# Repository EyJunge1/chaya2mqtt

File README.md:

Languages: **🇬🇧** | [🇩🇪](./.github/i18n/README.de.md)

Send a little heart to someone special—no matter how far away they are.

Chaya2MQTT pairs two people over [Waveshare ESP32-S3 e-paper displays](https://docs.waveshare.com/ESP32-S3-ePaper-1.54G)—each can have more than one board (home, office, …).

Press the button on yours and a red heart appears on theirs.

Every display keeps track of the hearts you have sent and received, while MQTT quietly carries them between you.

### Product

| Online                                                    | Product title                                             | SoftAP setup                                       | Offline                                                       | Power-off                                          |
| --------------------------------------------------------- | --------------------------------------------------------- | -------------------------------------------------- | ------------------------------------------------------------- | -------------------------------------------------- |
|  |  |  |  |  |

> [!NOTE]
> Open the [web flasher](https://eyjunge1.github.io/chaya2mqtt/) in Chrome or Edge, connect USB-C, and install.

### Case

Printable snap-fit case (battery + USB-only): [MakerWorld](https://makerworld.com/de/models/3505578-waveshare-esp32-s3-epaper-1-54-case-chaya2mqtt#profileId-4005122).

Remove the rear SPI header and the speaker before assembly.

## License

[GNU GPL v3.0 only](LICENSE)

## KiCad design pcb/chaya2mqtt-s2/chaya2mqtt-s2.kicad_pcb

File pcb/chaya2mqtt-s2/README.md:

# chaya2mqtt-s2 Rev A2

Compact four-layer 46.0 × 45.0 mm board for ESP32-S2-MINI-2-N4R2 and
GDEM0154F61H. The e-paper display is mounted at the front of the enclosure,
USB-C sits at the lower edge on the rear, and the illuminated button is
connected through J3.

## Target hardware

- ESP32-S2-MINI-2-N4R2: Wi-Fi, native USB, no Bluetooth, 4 MB flash, 2 MB PSRAM
- GDEM0154F61H: 1.54 inch, 200×200, black/white/red/yellow, SSD2681
- USB-C at the rear; display at the front; wired red LED ring button
- Four layers: F.Cu / In1.Cu GND / In2.Cu 3V3 / B.Cu

## Electrical blocks

- USB-C with 5.1 kΩ CC resistors, ESD protection, PTC, and 22 Ω series resistors
- TLV75733PDBVR (1 A) with input/output decoupling
- EN/BOOT, reset/boot buttons, and five test points
- 24-pin 0.5 mm FPC for the raw panel
- SSD2681 boost circuit according to GDEM0154F61H Rev 1.0 dated 2026-05-15

## Status

- The schematic is electrically complete; KiCad 10 ERC reports 0 violations.
- Unused MCU/panel pins are explicitly marked as `No Connect`.
- The 46 × 45 mm layout is fully routed; KiCad 10 DRC reports
  0 violations and 0 unconnected items.
- In1 contains a GND plane, and In2 contains a 3V3 plane. Both start below
  the ESP32 antenna keepout.
- KiCad sources, BOM, CPL, and manufacturing exports are located in `production/`.
- Two M2 holes at the bottom; the top remains free of holes due to the official
  antenna keepout.
- The board is a prototype. Electrical bring-up, e-paper high-voltage
  measurements, USB signal integrity testing, mechanical FPC/enclosure checks,
  and a 2.4 GHz RF test are required before a production order.

`../tools/generate_chaya2mqtt_s2_schematic.py` generates the schematic
reproducibly. `../tools/apply_schematic_netlist.py` maps the XML netlist
unambiguously onto the PCB, including duplicated footprint pads.
Manufacturing data, PDF, BOM, ERC, and DRC are exported with `kicad-cli`.

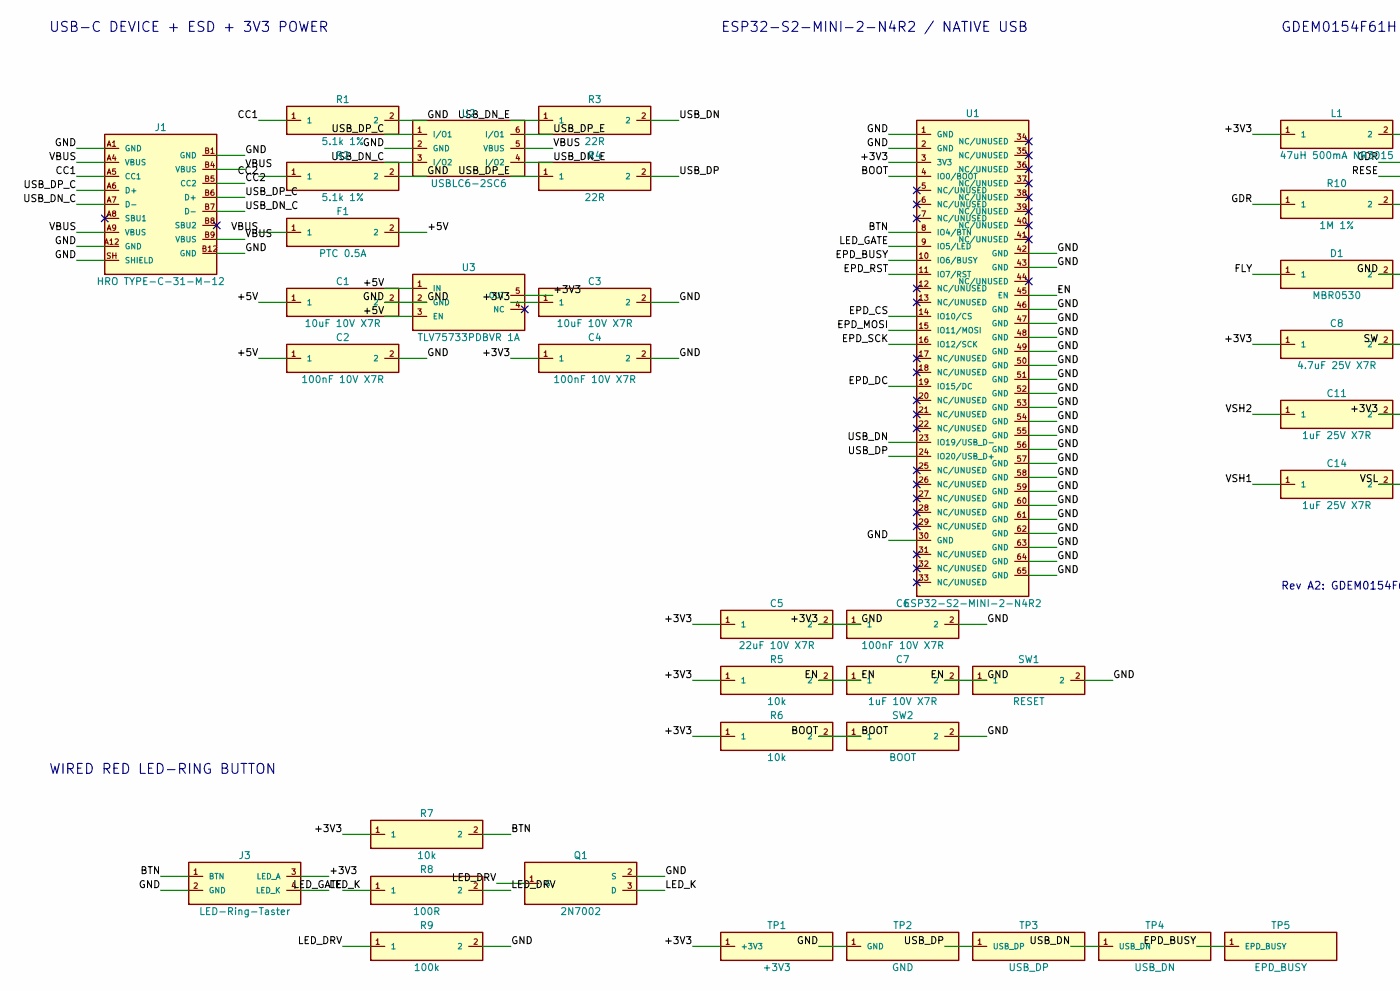
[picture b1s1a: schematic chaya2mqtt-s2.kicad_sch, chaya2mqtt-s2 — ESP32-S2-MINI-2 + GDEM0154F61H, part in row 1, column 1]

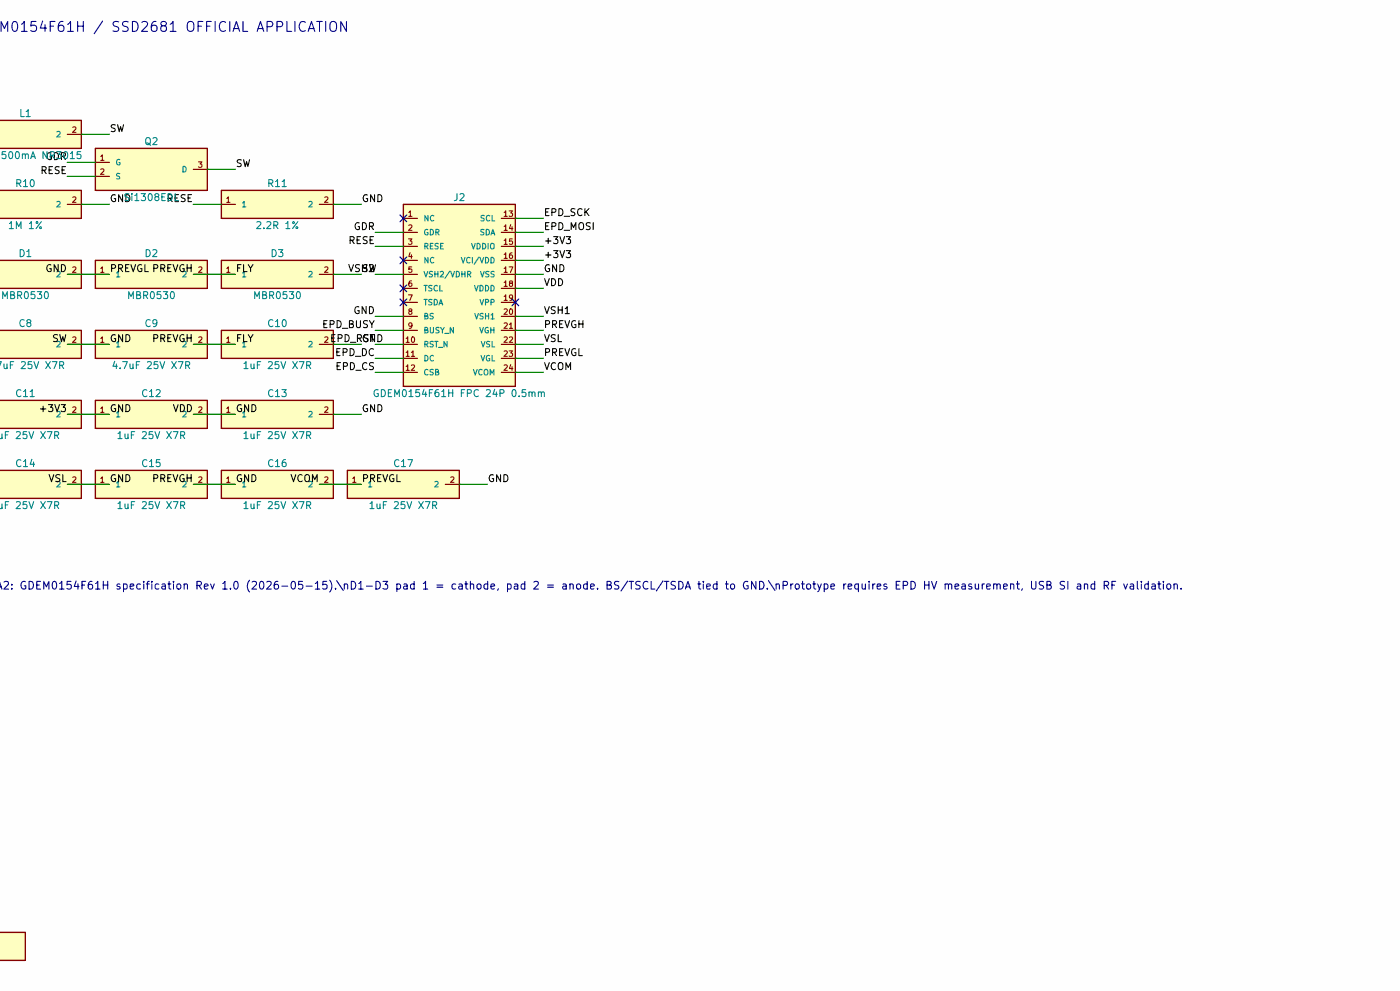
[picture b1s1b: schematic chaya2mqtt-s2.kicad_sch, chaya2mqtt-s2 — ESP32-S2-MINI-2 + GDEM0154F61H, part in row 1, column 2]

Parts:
C1, C3: 10uF 10V X7R; C_0805_2012Metric
C2, C4, C6: 100nF 10V X7R; C_0402_1005Metric
C5: 22uF 10V X7R; C_0805_2012Metric
C7: 1uF 10V X7R; C_0603_1608Metric
C8, C9: 4.7uF 25V X7R; C_0805_2012Metric
C10, C11, C12, C13, C14, C15, C16, C17: 1uF 25V X7R; C_0603_1608Metric
D1, D2, D3: MBR0530; D_SOD-123
F1: PTC 0.5A; Fuse_1206_3216Metric
J1: HRO TYPE-C-31-M-12; USB_C_Receptacle_HRO_TYPE-C-31-M-12; MPN TYPE-C-31-M-12
J2: GDEM0154F61H FPC 24P 0.5mm; Hirose_FH12-24S-0.5SH_1x24-1MP_P0.50mm_Horizontal; MPN GDEM0154F61H
J3: LED-Ring-Taster; JST_SH_SM04B-SRSS-TB_1x04-1MP_P1.00mm_Horizontal
L1: 47uH 500mA NR3015; L_Taiyo-Yuden_NR-30xx
Q1: 2N7002; SOT-23
Q2: Si1308EDL; SOT-323_SC-70; MPN SI1308EDL-T1-GE3
R1, R2: 5.1k 1%; R_0402_1005Metric
R3, R4: 22R; R_0402_1005Metric
R5, R6, R7: 10k; R_0402_1005Metric
R8: 100R; R_0402_1005Metric
R9: 100k; R_0402_1005Metric
R10: 1M 1%; R_0402_1005Metric
R11: 2.2R 1%; R_0603_1608Metric
SW1: RESET; SW_Push_1P1T_NO_CK_KMR2
SW2: BOOT; SW_Push_1P1T_NO_CK_KMR2
TP1: +3V3; TestPoint_Pad_D1.0mm
TP2: GND; TestPoint_Pad_D1.0mm
TP3: USB_DP; TestPoint_Pad_D1.0mm
TP4: USB_DN; TestPoint_Pad_D1.0mm
TP5: EPD_BUSY; TestPoint_Pad_D1.0mm
U1: ESP32-S2-MINI-2-N4R2; ESP32-S2-MINI-1; MPN ESP32-S2-MINI-2-N4R2
U2: USBLC6-2SC6; SOT-23-6; MPN USBLC6-2SC6
U3: TLV75733PDBVR 1A; SOT-23-5; MPN TLV75733PDBVR

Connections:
/+3V3: C3.1, C4.1, C5.1, C6.1, C8.1, C12.1, J2.15 (VDDIO), J2.16 (VCI/VDD), J3.3 (LED_A), L1.1, R5.1, R6.1, R7.1, TP1.1 (+3V3_1), U1.3 (3V3), U3.5 (OUT)
/+5V: C1.1, C2.1, F1.2, U3.1 (IN), U3.3 (EN)
/BOOT: R6.2, SW2.1, U1.4 (IO0/BOOT)
/BTN: J3.1 (BTN), R7.2, U1.8 (IO4/BTN)
/CC1: J1.A5 (CC1), R1.1
/CC2: J1.B5 (CC2), R2.1
/EN: C7.1, R5.2, SW1.1, U1.45 (EN)
/EPD_BUSY: J2.9 (BUSY_N), TP5.1 (EPD_BUSY_1), U1.10 (IO6/BUSY)
/EPD_CS: J2.12 (CSB), U1.14 (IO10/CS)
/EPD_DC: J2.11 (DC), U1.19 (IO15/DC)
/EPD_MOSI: J2.14 (SDA), U1.15 (IO11/MOSI)
/EPD_RST: J2.10 (RST_N), U1.11 (IO7/RST)
/EPD_SCK: J2.13 (SCL), U1.16 (IO12/SCK)
/FLY: C9.2, D1.1, D2.2
/GDR: J2.2 (GDR), Q2.1 (G), R10.1
/GND: C1.2, C2.2, C3.2, C4.2, C5.2, C6.2, C7.2, C8.2, C10.2, C11.2, C12.2, C13.2, C14.2, C15.2, C17.2, D2.1, J1.A1 (GND), J1.A12 (GND), J1.B1 (GND), J1.B12 (GND), J1.SH (SHIELD), J2.8 (BS), J2.17 (VSS), J3.2 (GND), Q1.2 (S), R1.2, R2.2, R9.2, R10.2, R11.2, SW1.2, SW2.2, TP2.1 (GND_1), U1.1 (GND), U1.2 (GND), U1.30 (GND), U1.42 (GND), U1.43 (GND), U1.46 (GND), U1.47 (GND), U1.48 (GND), U1.49 (GND), U1.50 (GND), U1.51 (GND), U1.52 (GND), U1.53 (GND), U1.54 (GND), U1.55 (GND), U1.56 (GND), U1.57 (GND), U1.58 (GND), U1.59 (GND), U1.60 (GND), U1.61 (GND), U1.62 (GND), U1.63 (GND), U1.64 (GND), U1.65 (GND), U2.2 (GND), U3.2 (GND)
/LED_DRV: Q1.1 (G), R8.2, R9.1
/LED_GATE: R8.1, U1.9 (IO5/LED)
/LED_K: J3.4 (LED_K), Q1.3 (D)
/PREVGH: C10.1, C16.1, D3.1, J2.21 (VGH)
/PREVGL: C16.2, D1.2, J2.23 (VGL)
/RESE: J2.3 (RESE), Q2.2 (S), R11.1
/SW: C9.1, D3.2, L1.2, Q2.3 (D)
/USB_DN: R3.2, TP4.1 (USB_DN_1), U1.23 (IO19/USB_D-)
/USB_DN_C: J1.A7 (D-), J1.B7 (D-), U2.3 (I/O2)
/USB_DN_E: R3.1, U2.4 (I/O2)
/USB_DP: R4.2, TP3.1 (USB_DP_1), U1.24 (IO20/USB_D+)
/USB_DP_C: J1.A6 (D+), J1.B6 (D+), U2.1 (I/O1)
/USB_DP_E: R4.1, U2.6 (I/O1)
/VBUS: F1.1, J1.A4 (VBUS), J1.A9 (VBUS), J1.B4 (VBUS), J1.B9 (VBUS), U2.5 (VBUS)
/VCOM: C17.1, J2.24 (VCOM)
/VDD: C13.1, J2.18 (VDDD)
/VSH1: C14.1, J2.20 (VSH1)
/VSH2: C11.1, J2.5 (VSH2/VDHR)
/VSL: C15.1, J2.22 (VSL)

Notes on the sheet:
ESP32-S2-MINI-2-N4R2 / NATIVE USB
GDEM0154F61H / SSD2681 OFFICIAL APPLICATION
WIRED RED LED-RING BUTTON
USB-C DEVICE + ESD + 3V3 POWER
Rev A2: GDEM0154F61H specification Rev 1.0 (2026-05-15).\nD1-D3 pad 1 = cathode, pad 2 = anode. BS/TSCL/TSDA tied to GND.\nPrototype requires EPD HV measurement, USB SI and RF validation.

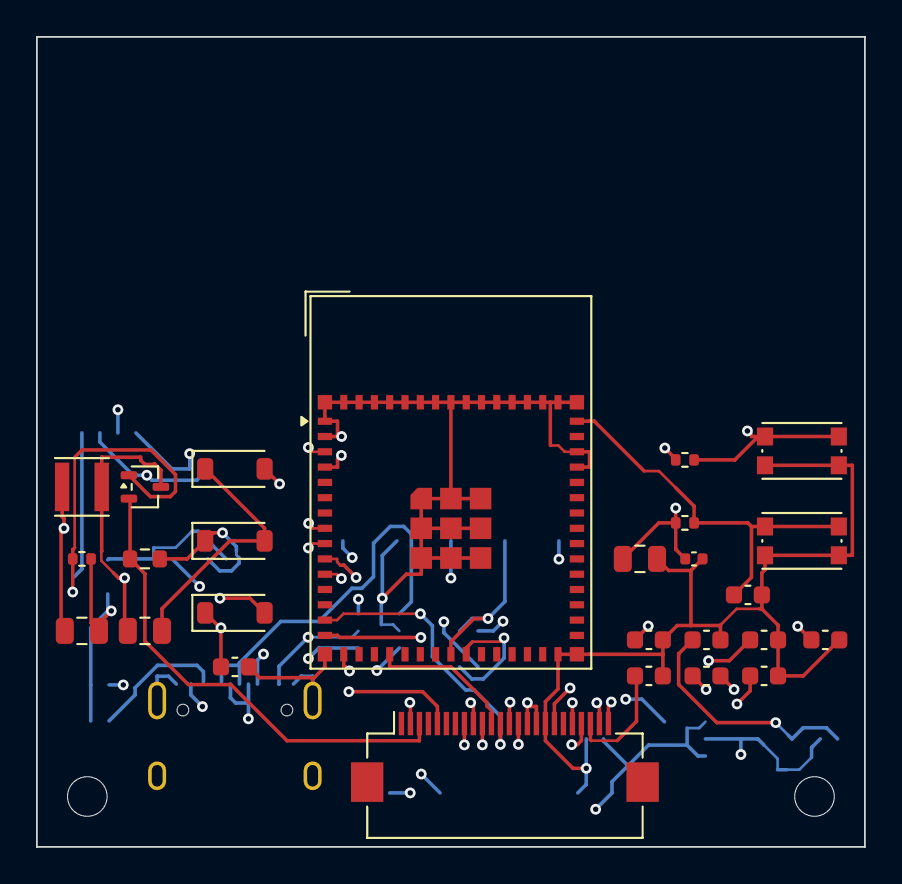
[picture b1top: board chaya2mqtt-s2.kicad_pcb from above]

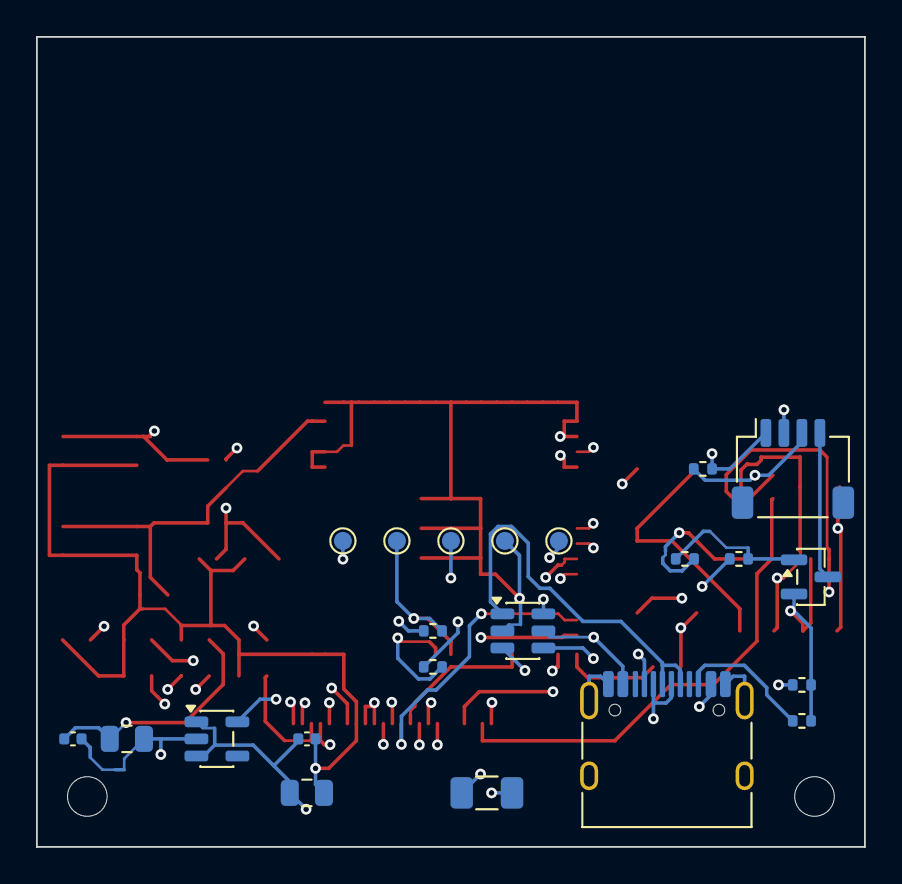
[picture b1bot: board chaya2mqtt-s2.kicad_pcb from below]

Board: 4 copper layers, 46.0 x 45.0 mm, 50 parts (22 on the bottom side), 35 nets.

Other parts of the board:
H1, H2: M2; MountingHole_2.2mm_M2

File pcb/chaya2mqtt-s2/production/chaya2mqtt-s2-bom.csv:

"Reference","Value","Footprint","Manufacturer","MPN","Datasheet","Quantity","DNP"
"C1,C3","10uF 10V X7R","Capacitor_SMD:C_0805_2012Metric","","","","2",""
"C2,C4,C6","100nF 10V X7R","Capacitor_SMD:C_0402_1005Metric","","","","3",""
"C5","22uF 10V X7R","Capacitor_SMD:C_0805_2012Metric","","","","1",""
"C7","1uF 10V X7R","Capacitor_SMD:C_0603_1608Metric","","","","1",""
"C8,C9","4.7uF 25V X7R","Capacitor_SMD:C_0805_2012Metric","","","","2",""
"C10-C17","1uF 25V X7R","Capacitor_SMD:C_0603_1608Metric","","","","8",""
"D1-D3","MBR0530","Diode_SMD:D_SOD-123","","","","3",""
"F1","PTC 0.5A","Fuse:Fuse_1206_3216Metric","","","","1",""
"J1","HRO TYPE-C-31-M-12","Connector_USB:USB_C_Receptacle_HRO_TYPE-C-31-M-12","HRO","TYPE-C-31-M-12","http://www.krhro.com/uploads/soft/180320/1-1P320120243.pdf","1",""
"J2","GDEM0154F61H FPC 24P 0.5mm","Connector_FFC-FPC:Hirose_FH12-24S-0.5SH_1x24-1MP_P0.50mm_Horizontal","Good Display","GDEM0154F61H","https://www.good-display.com/companyfile/2085.html","1",""
"J3","LED-Ring-Taster","Connector_JST:JST_SH_SM04B-SRSS-TB_1x04-1MP_P1.00mm_Horizontal","","","","1",""
"L1","47uH 500mA NR3015","Inductor_SMD:L_Taiyo-Yuden_NR-30xx","","","","1",""
"Q1","2N7002","Package_TO_SOT_SMD:SOT-23","","","","1",""
"Q2","Si1308EDL","Package_TO_SOT_SMD:SOT-323_SC-70","Vishay","SI1308EDL-T1-GE3","https://www.vishay.com/docs/63399/si1308edl.pdf","1",""
"R1,R2","5.1k 1%","Resistor_SMD:R_0402_1005Metric","","","","2",""
"R3,R4","22R","Resistor_SMD:R_0402_1005Metric","","","","2",""
"R5-R7","10k","Resistor_SMD:R_0402_1005Metric","","","","3",""
"R8","100R","Resistor_SMD:R_0402_1005Metric","","","","1",""
"R9","100k","Resistor_SMD:R_0402_1005Metric","","","","1",""
"R10","1M 1%","Resistor_SMD:R_0402_1005Metric","","","","1",""
"R11","2.2R 1%","Resistor_SMD:R_0603_1608Metric","","","","1",""
"SW1","RESET","Button_Switch_SMD:SW_Push_1P1T_NO_CK_KMR2","","","","1",""
"SW2","BOOT","Button_Switch_SMD:SW_Push_1P1T_NO_CK_KMR2","","","","1",""
"TP1","+3V3","TestPoint:TestPoint_Pad_D1.0mm","","","","1",""
"TP2","GND","TestPoint:TestPoint_Pad_D1.0mm","","","","1",""
"TP3","USB_DP","TestPoint:TestPoint_Pad_D1.0mm","","","","1",""
"TP4","USB_DN","TestPoint:TestPoint_Pad_D1.0mm","","","","1",""
"TP5","EPD_BUSY","TestPoint:TestPoint_Pad_D1.0mm","","","","1",""
"U1","ESP32-S2-MINI-2-N4R2","RF_Module:ESP32-S2-MINI-1","Espressif","ESP32-S2-MINI-2-N4R2","https://documentation.espressif.com/esp32-s2-mini-2_esp32-s2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","1",""
"U2","USBLC6-2SC6","Package_TO_SOT_SMD:SOT-23-6","STMicroelectronics","USBLC6-2SC6","https://www.st.com/resource/en/datasheet/usblc6-2.pdf","1",""
"U3","TLV75733PDBVR 1A","Package_TO_SOT_SMD:SOT-23-5","Texas Instruments","TLV75733PDBVR","https://www.ti.com/lit/ds/symlink/tlv757p.pdf","1",""

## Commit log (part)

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2026-05-18 Refactor MQTT reconnection logic to improve variable handling and logging
    This commit updates the MQTT reconnection logic by refining variable declarations for clarity and ensuring that the remaining backoff time and period are explicitly cast to void. These changes enhanc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
2026-05-18 Update platformio.ini, README, and documentation for improved clarity and functionality
    This commit modifies the platformio.ini file to set the CPU frequency to match runtime settings, enhancing performance consistency. The README is updated to include a new section on security and thre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
2026-05-18 Refactor Wi-Fi scanning logic to utilize WiFiScan API for improved performance
    This commit removes the unused `s_wifiScanApWorkRecords` array and updates the Wi-Fi scanning process to leverage the Arduino core's `WiFiScan` API. The changes streamline the retrieval of access poi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
2026-05-18 Refactor CSRF token handling in Wi-Fi connection form for improved consistency
    This commit simplifies the CSRF token handling in the Wi-Fi connection form by removing the conditional check for AP mode and ensuring the token is always included. This change enhances code clarity 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
2026-05-18 Enhance CSRF token integration in Wi-Fi connection forms for improved security
    This commit adds CSRF token fields to both the Wi-Fi connection abort and commit forms, ensuring consistent security practices across the application. The changes enhance the protection against cross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
2026-05-18 Implement POST method for logout functionality and enhance CSRF protection
    This commit modifies the logout functionality to use the POST method instead of GET, improving security by requiring CSRF token validation. The logout route now checks for user authentication and CSR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
2026-05-27 Implement device pairing functionality with MQTT topic management
    This commit introduces a new device pairing feature that allows two devices to connect using a unique 6-character device ID derived from their MAC addresses. The pairing process is facilitated throug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
2026-05-27 Refactor MQTT and display logic for improved command handling and state management
    This commit introduces several enhancements across the MQTT and display modules. Key changes include the removal of the unused `MqttReconnect` command in favor of a new `ChayaSendRequested` command, 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
2026-05-27 Update documentation and enhance security model for Chaya2MQTT
    This commit expands the README and various documentation files to provide a clearer overview of the Chaya2MQTT project, including detailed descriptions of the system architecture, module responsibili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
2026-05-27 Update security documentation and enhance HTTP response headers
    This commit updates the SECURITY.md file to change the session cookie attribute from SameSite=Strict to SameSite=Lax, improving compatibility with third-party contexts. Additionally, it enhances the 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
2026-05-27 Enhance build configuration and documentation for Chaya2MQTT
    This commit updates the platformio.ini file to define a default environment for production builds and adds a new native environment for testing with Unity. The README is modified to reflect the new b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
2026-05-27 Refactor display driver integration and update documentation for GxEPD2
    This commit replaces the custom EpdDriver154Z90c with the GxEPD2 library as a PlatformIO dependency, streamlining the display driver implementation. The platformio.ini file is updated to include the 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
2026-05-27 Enhance documentation and improve configuration handling for Chaya2MQTT
    This commit updates the architecture documentation to include a new mutex for MQTT configuration and clarifies the initialization sequence for the display driver. It also corrects the stack size for 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
2026-05-27 Refactor MQTT configuration and clean up unused code
    This commit refines the MQTT configuration by moving the `kMqttClientTaskStackBytes` constant to the task configuration header for better organization. It also removes the now-unnecessary button and 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
2026-05-27 Refactor code structure and remove unused files for improved maintainability
    This commit streamlines the codebase by removing several unused files, including `ip_format.h`, `log_tag.h`, and TLS-related files, which enhances overall project clarity. Additionally, it updates in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
2026-05-27 Update file paths and enhance documentation for configuration and modules
    This commit modifies the file paths for versioning and configuration headers, moving `version.h` to `config/version.h` and updating related documentation accordingly. It also clarifies module respons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
2026-05-27 Refactor authentication module and update file paths for improved organization
    This commit restructures the authentication module by moving header files to a dedicated `auth` directory, enhancing code organization and maintainability. It also updates various source files to ref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
2026-05-27 Update documentation to reflect new file paths and enhance clarity
    This commit updates the documentation across several files to reflect the restructuring of the project, including the movement of authentication and routing files into dedicated directories. It clari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
2026-06-08 Enhance documentation and improve OTA task handling
    This commit updates the README and SECURITY.md files to clarify the open nature of the `Chaya2MQTT` access point during initial setup, emphasizing its use without a password. Additionally, it introdu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
2026-06-08 Refactor web routing and improve captive portal handling
    This commit modifies the web routing logic to redirect users to the Wi-Fi settings page when in AP mode, enhancing user experience. Additionally, it simplifies the captive portal handling in the web 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
